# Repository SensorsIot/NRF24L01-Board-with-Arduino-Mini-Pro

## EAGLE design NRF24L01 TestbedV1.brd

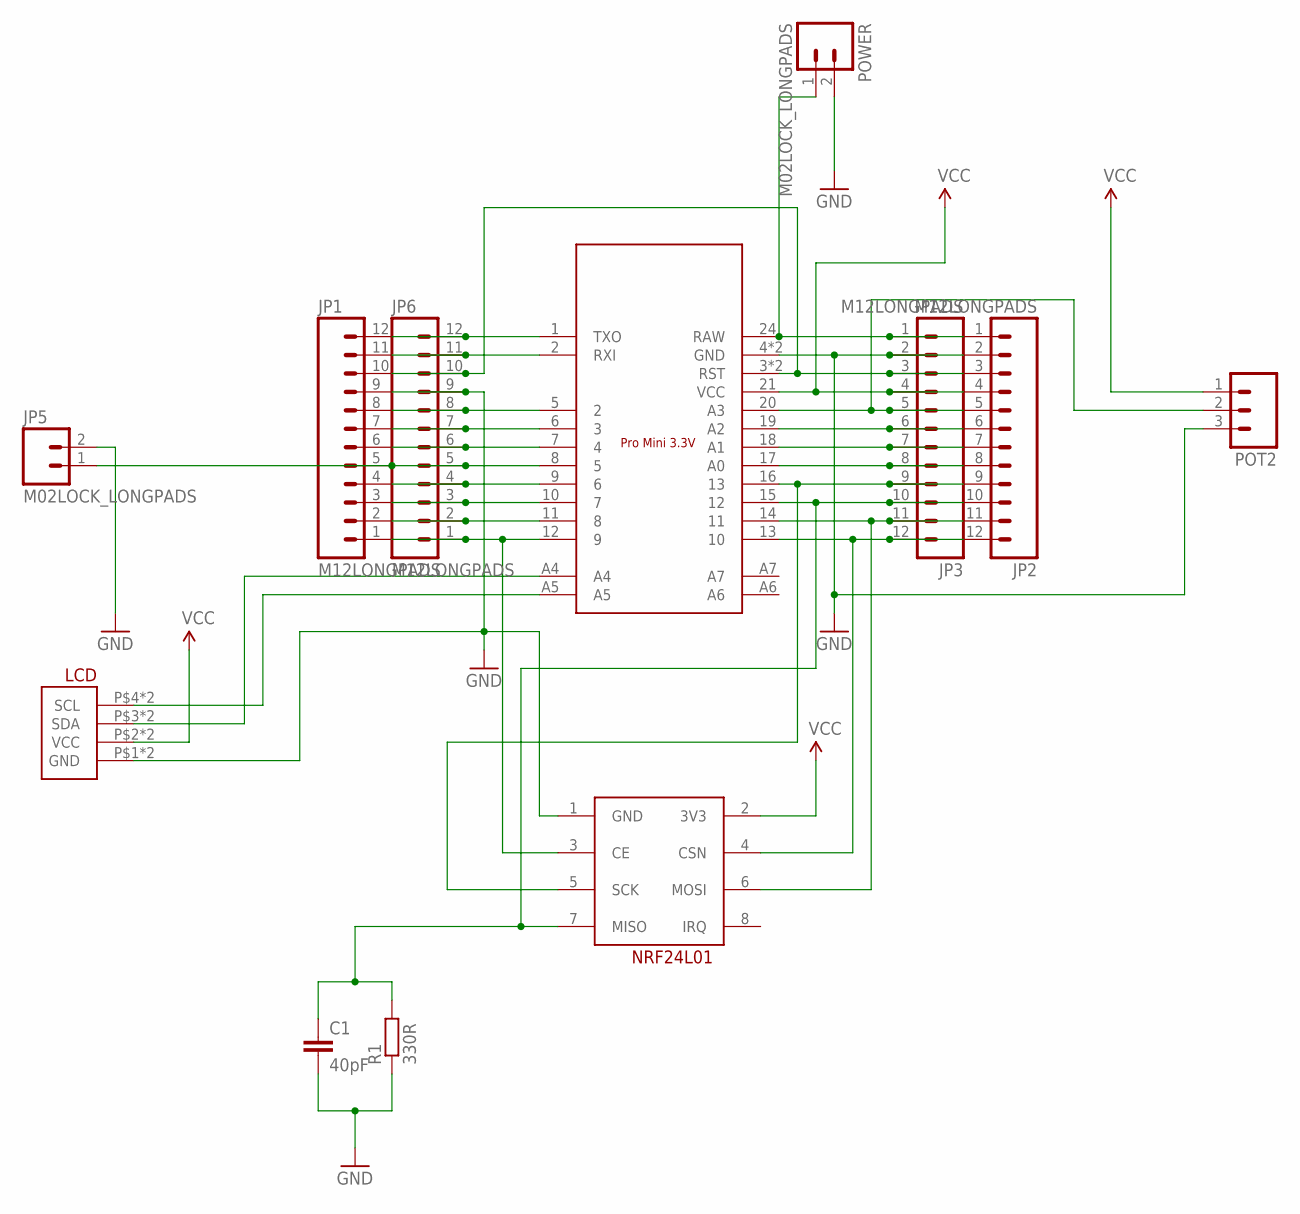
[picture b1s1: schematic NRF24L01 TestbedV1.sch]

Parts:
C1: 40pF; C1206
JP1, JP2, JP3, JP6: M12LONGPADS; 1X12_LONGPADS
JP5: M02LOCK_LONGPADS; 1X02_LOCK_LONGPADS
POT2: M03LONGPADS; 1X03_LONGPADS
POWER: M02LOCK_LONGPADS; 1X02_LOCK_LONGPADS
R1: 330R; R1206
U$1: ARDUINO_PRO_MINI_3V3
U$2: NRF24L01BOARD
U$3: I2C-LCD

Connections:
GND: C1.2, JP1.9, JP2.2, JP3.2, JP5.2, JP6.9, POT2.3, POWER.2, R1.1, U$1.4 (GND), U$1.23 (GND), U$2.1 (GND), U$3.P$1 (GND), U$3.S$1 (GND)
unnamed: JP2.5, JP3.5, POT2.2, U$1.20 (A3)
unnamed: JP1.12, JP6.12, U$1.1 (TXO)
unnamed: JP1.11, JP6.11, U$1.2 (RXI)
unnamed: JP1.4, JP6.4, U$1.9 (6)
unnamed: JP1.8, JP6.8, U$1.5 (2)
unnamed: JP1.10, JP2.3, JP3.3, JP6.10, U$1.3 (RST), U$1.22 (RST)
unnamed: JP1.7, JP6.7, U$1.6 (3)
unnamed: JP1.6, JP6.6, U$1.7 (4)
unnamed: JP1.5, JP5.1, JP6.5, U$1.8 (5)
unnamed: JP1.3, JP6.3, U$1.10 (7)
unnamed: JP1.2, JP6.2, U$1.11 (8)
unnamed: JP1.1, JP6.1, U$1.12 (9), U$2.3 (CE)
unnamed: JP2.1, JP3.1, POWER.1, U$1.24 (RAW)
unnamed: JP2.6, JP3.6, U$1.19 (A2)
unnamed: JP2.7, JP3.7, U$1.18 (A1)
unnamed: JP2.8, JP3.8, U$1.17 (A0)
unnamed: JP2.9, JP3.9, U$1.16 (13), U$2.5 (SCK)
unnamed: C1.1, JP2.10, JP3.10, R1.2, U$1.15 (12), U$2.7 (MISO)
unnamed: JP2.11, JP3.11, U$1.14 (11), U$2.6 (MOSI)
unnamed: JP2.12, JP3.12, U$1.13 (10), U$2.4 (CSN)
unnamed: U$1.A4, U$3.P$3 (SDA), U$3.S$3 (SDA)
unnamed: U$1.A5, U$3.P$4 (SCL), U$3.S$4 (SCL)
VCC: JP2.4, JP3.4, POT2.1, U$1.21 (VCC), U$2.2 (3V3), U$3.P$2 (VCC), U$3.S$2 (VCC)

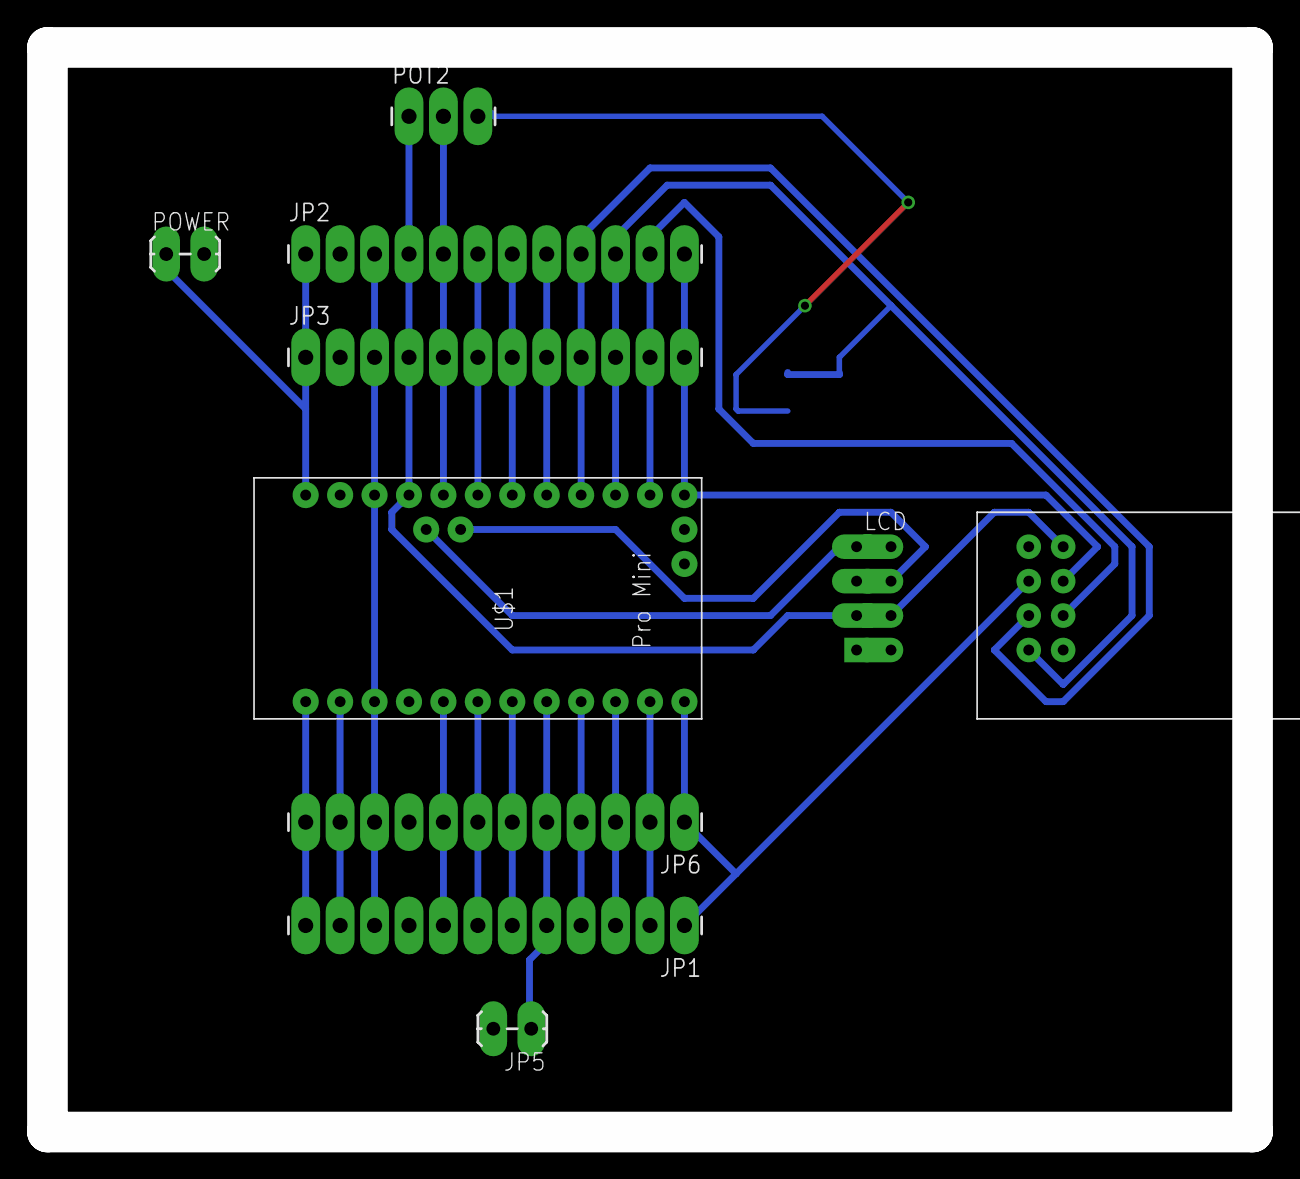
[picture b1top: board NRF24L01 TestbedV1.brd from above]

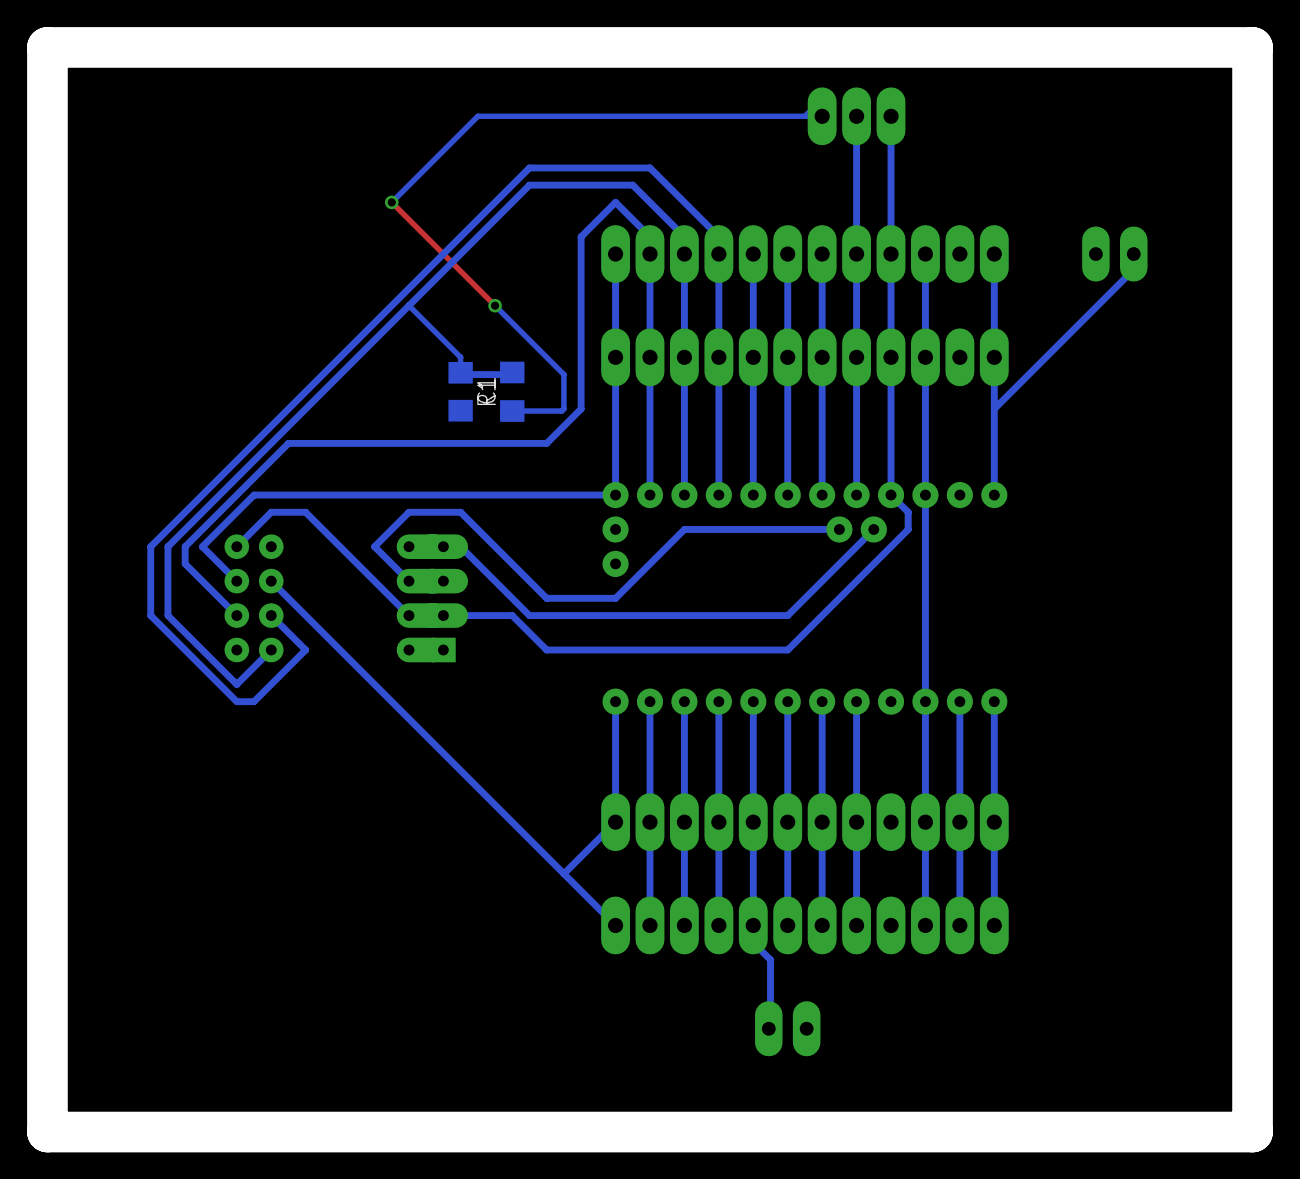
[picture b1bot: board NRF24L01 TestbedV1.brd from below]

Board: 2 copper layers, 88.9 x 80.0 mm, 12 parts (2 on the bottom side), 24 nets.

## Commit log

2016-04-16 :circus_tent: Added .gitattributes & .gitignore files

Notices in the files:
parts and their libraries:
SparkFun-Connectors: Licensing: Creative Commons ShareAlike 4.0 International - https://creativecommons.org/licenses/by-sa/4.0
